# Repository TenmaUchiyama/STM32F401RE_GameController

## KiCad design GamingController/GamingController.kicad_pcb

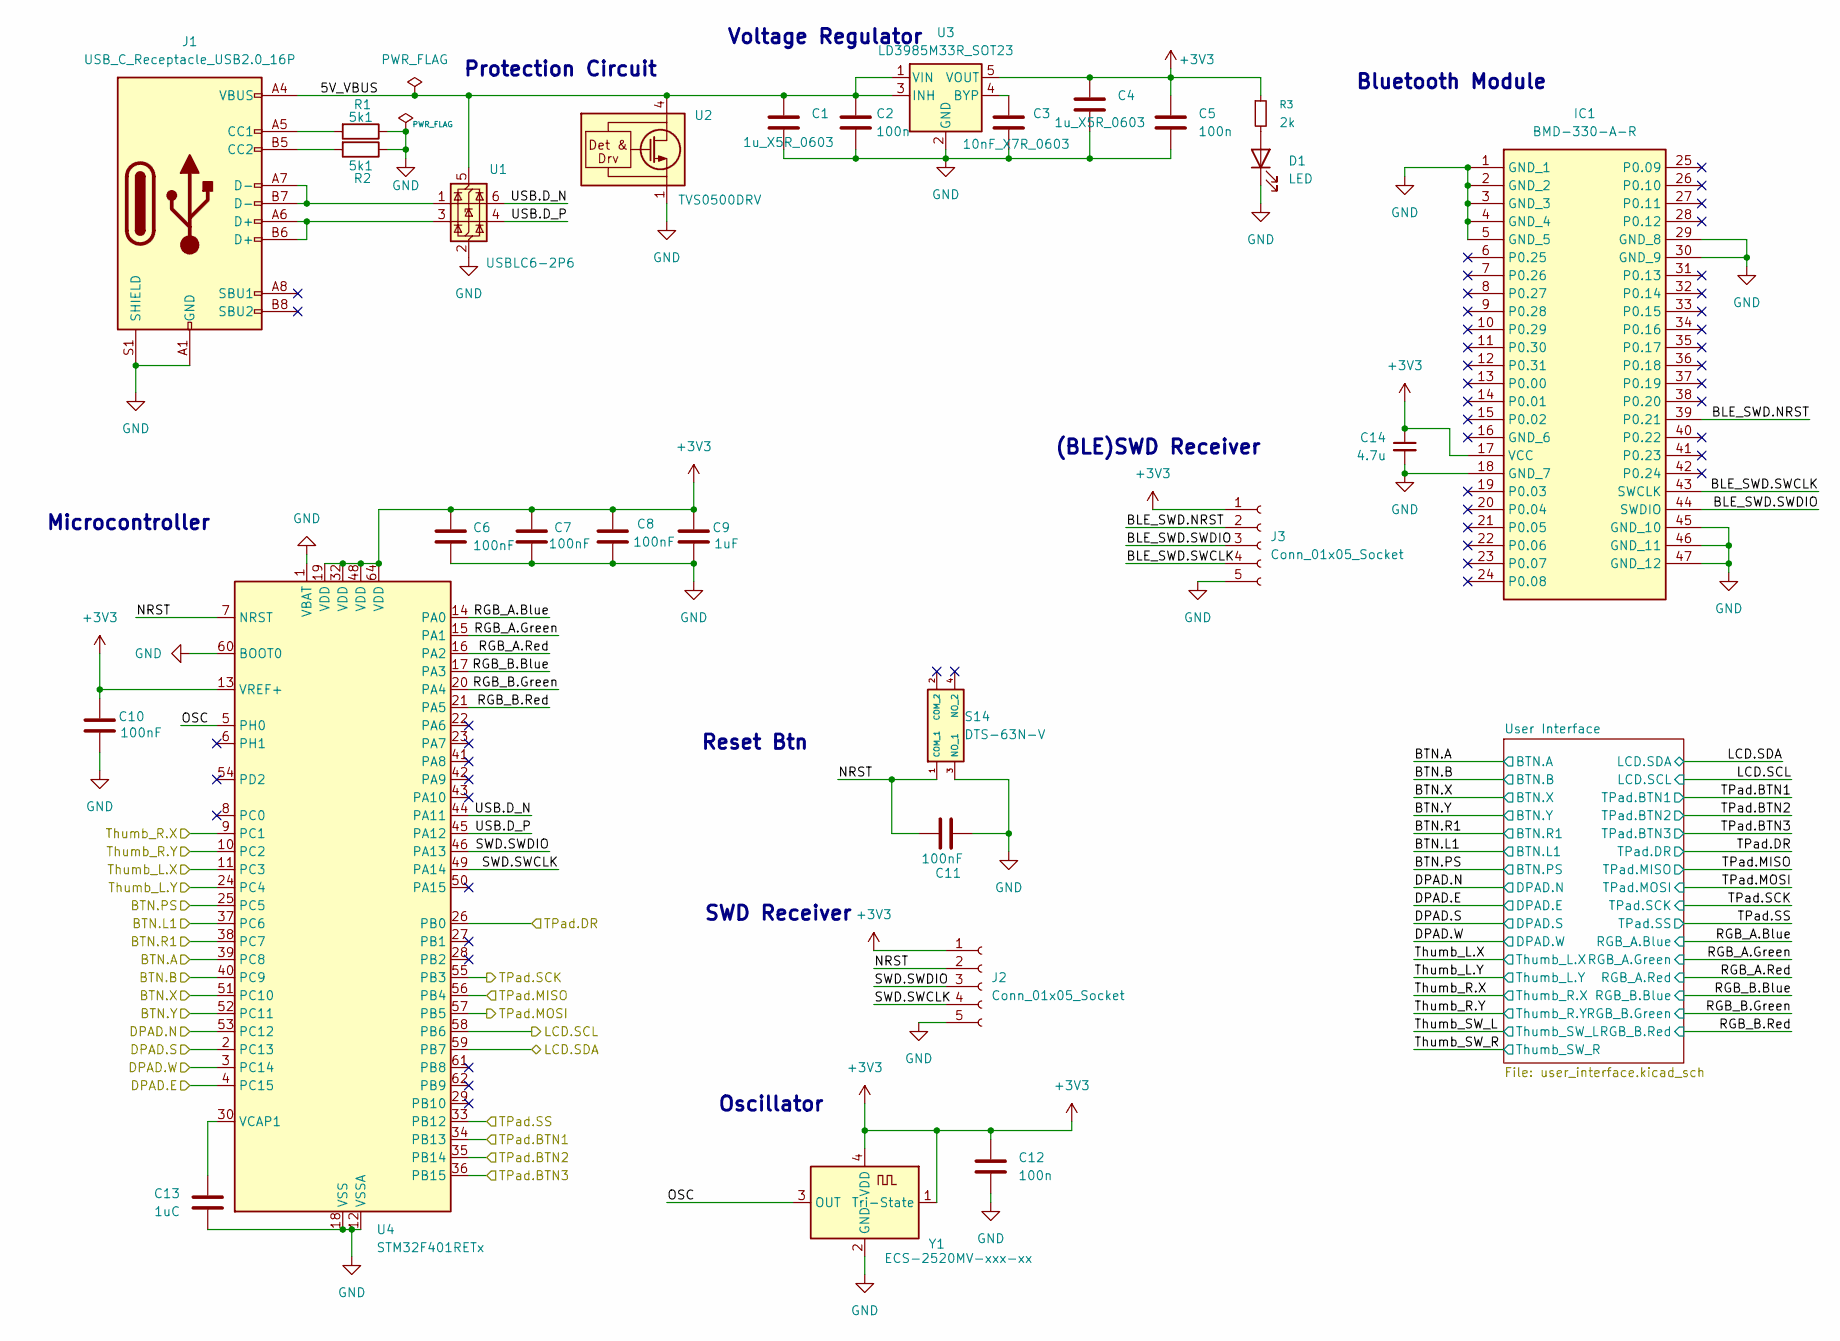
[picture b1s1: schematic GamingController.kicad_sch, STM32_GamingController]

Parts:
C1, C4: 1u_X5R_0603; C_0201_0603Metric
C2, C5, C12: 100n; C_0201_0603Metric
C3: 10nF_X7R_0603; C_0201_0603Metric
C6, C7, C8, C10, C11: 100nF; C_0201_0603Metric
C9: 1uF; C_0201_0603Metric
C13: 1uC; C_0201_0603Metric
C14: 4.7u; C_0201_0603Metric
D1: LED; LED_0201_0603Metric
IC1: BMD-330-A-R; BMD330AR; Mouser Part Number 377-BMD-330-A-R
J1: USB_C_Receptacle_USB2.0_16P; USB_C_Receptacle_JAE_DX07S016JA1R1500
J2, J3: Conn_01x05_Socket; PinSocket_1x05_P2.00mm_Horizontal
R1, R2: 5k1; R_0201_0603Metric
R3: 2k; R_0201_0603Metric
S14: DTS-63N-V; DTS63NV; Mouser Part Number 113-DTS-63N-V
U1: USBLC6-2P6; SOT-666
U2: TVS0500DRV; WSON-6-1EP_2x2mm_P0.65mm_EP1x1.6mm
U3: LD3985M33R_SOT23; SOT-23-5
U4: STM32F401RETx; LQFP-64_10x10mm_P0.5mm
Y1: ECS-2520MV-xxx-xx; Oscillator_SMD_ECS_2520MV-xxx-xx-4Pin_2.5x2.0mm

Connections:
+3V3: C4.1, C5.1, C6.1, C7.1, C8.1, C9.1, C10.1, C12.1, C14.1, IC1.17 (VCC), J2.1, J3.1, R3.1, U3.5 (VOUT), U4.13 (VREF+), U4.19 (VDD), U4.32 (VDD), U4.48 (VDD), U4.64 (VDD), Y1.1 (Tri-State), Y1.4 (VDD); also elsewhere on the board
/5V_VBUS: C1.1, C2.1, J1.A4 (VBUS), J1.A9 (VBUS), J1.B4 (VBUS), J1.B9 (VBUS), U1.5 (VBUS), U2.4 (IN), U2.5 (IN), U2.6 (IN), U3.1 (VIN), U3.3 (INH)
/BLE_SWD.NRST: IC1.39 (P0.21), J3.2
/BLE_SWD.SWCLK: IC1.43 (SWCLK), J3.4
/BLE_SWD.SWDIO: IC1.44 (SWDIO), J3.3
/BTN.A: U4.39 (PC8); also elsewhere on the board
/BTN.B: U4.40 (PC9); also elsewhere on the board
/BTN.L1: U4.37 (PC6); also elsewhere on the board
/BTN.PS: U4.25 (PC5); also elsewhere on the board
/BTN.R1: U4.38 (PC7); also elsewhere on the board
/BTN.X: U4.51 (PC10); also elsewhere on the board
/BTN.Y: U4.52 (PC11); also elsewhere on the board
/DPAD.E: U4.4 (PC15); also elsewhere on the board
/DPAD.N: U4.53 (PC12); also elsewhere on the board
/DPAD.S: U4.2 (PC13); also elsewhere on the board
/DPAD.W: U4.3 (PC14); also elsewhere on the board
/LCD.SCL: U4.58 (PB6); also elsewhere on the board
/LCD.SDA: U4.59 (PB7); also elsewhere on the board
/NRST: C11.1, J2.2, S14.1 (COM_1), U4.7 (NRST)
/OSC: U4.5 (PH0), Y1.3 (OUT)
/RGB_A.Blue: U4.14 (PA0); also elsewhere on the board
/RGB_A.Green: U4.15 (PA1); also elsewhere on the board
/RGB_A.Red: U4.16 (PA2); also elsewhere on the board
/RGB_B.Blue: U4.17 (PA3); also elsewhere on the board
/RGB_B.Green: U4.20 (PA4); also elsewhere on the board
/RGB_B.Red: U4.21 (PA5); also elsewhere on the board
/SWD.SWCLK: J2.4, U4.49 (PA14)
/SWD.SWDIO: J2.3, U4.46 (PA13)
/TPad.BTN1: U4.34 (PB13); also elsewhere on the board
/TPad.BTN2: U4.35 (PB14); also elsewhere on the board
/TPad.BTN3: U4.36 (PB15); also elsewhere on the board
/TPad.DR: U4.26 (PB0); also elsewhere on the board
/TPad.MISO: U4.56 (PB4); also elsewhere on the board
/TPad.MOSI: U4.57 (PB5); also elsewhere on the board
/TPad.SCK: U4.55 (PB3); also elsewhere on the board
/TPad.SS: U4.33 (PB12); also elsewhere on the board
/Thumb_L.X: U4.11 (PC3); also elsewhere on the board
/Thumb_L.Y: U4.24 (PC4); also elsewhere on the board
/Thumb_R.X: U4.9 (PC1); also elsewhere on the board
/Thumb_R.Y: U4.10 (PC2); also elsewhere on the board
/USB.D_N: U1.6 (I/O1), U4.44 (PA11)
/USB.D_P: U1.4 (I/O2), U4.45 (PA12)
GND: C1.2, C2.2, C3.2, C4.2, C5.2, C6.2, C7.2, C8.2, C9.2, C10.2, C11.2, C12.2, C13.2, C14.2, D1.1 (K), IC1.1 (GND_1), IC1.2 (GND_2), IC1.3 (GND_3), IC1.4 (GND_4), IC1.5 (GND_5), IC1.18 (GND_7), IC1.29 (GND_8), IC1.30 (GND_9), IC1.45 (GND_10), IC1.46 (GND_11), IC1.47 (GND_12), J1.A1 (GND), J1.A12 (GND), J1.B1 (GND), J1.B12 (GND), J1.S1 (SHIELD), J2.5, J3.5, R1.1, R2.1, S14.3 (NO_1), U1.2 (GND), U2.1 (GND), U2.2 (GND), U2.3 (GND), U2.7 (GND), U3.2 (GND), U4.1 (VBAT), U4.12 (VSSA), U4.18 (VSS), U4.31 (VSS), U4.47 (VSS), U4.60 (BOOT0), U4.63 (VSS), Y1.2 (GND); also elsewhere on the board
unnamed: D1.2 (A), R3.2
unnamed: J1.A5 (CC1), R1.2
unnamed: J1.B5 (CC2), R2.2
unnamed: J1.A6 (D+), J1.B6 (D+), U1.3 (I/O2)
unnamed: J1.A7 (D-), J1.B7 (D-), U1.1 (I/O1)
unnamed: C3.1, U3.4 (BYP)
unnamed: C13.1, U4.30 (VCAP1)

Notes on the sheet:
Microcontroller
Bluetooth Module
Voltage Regulator
SWD Receiver
(BLE)SWD Receiver
Reset Btn
Protection Circuit
Oscillator

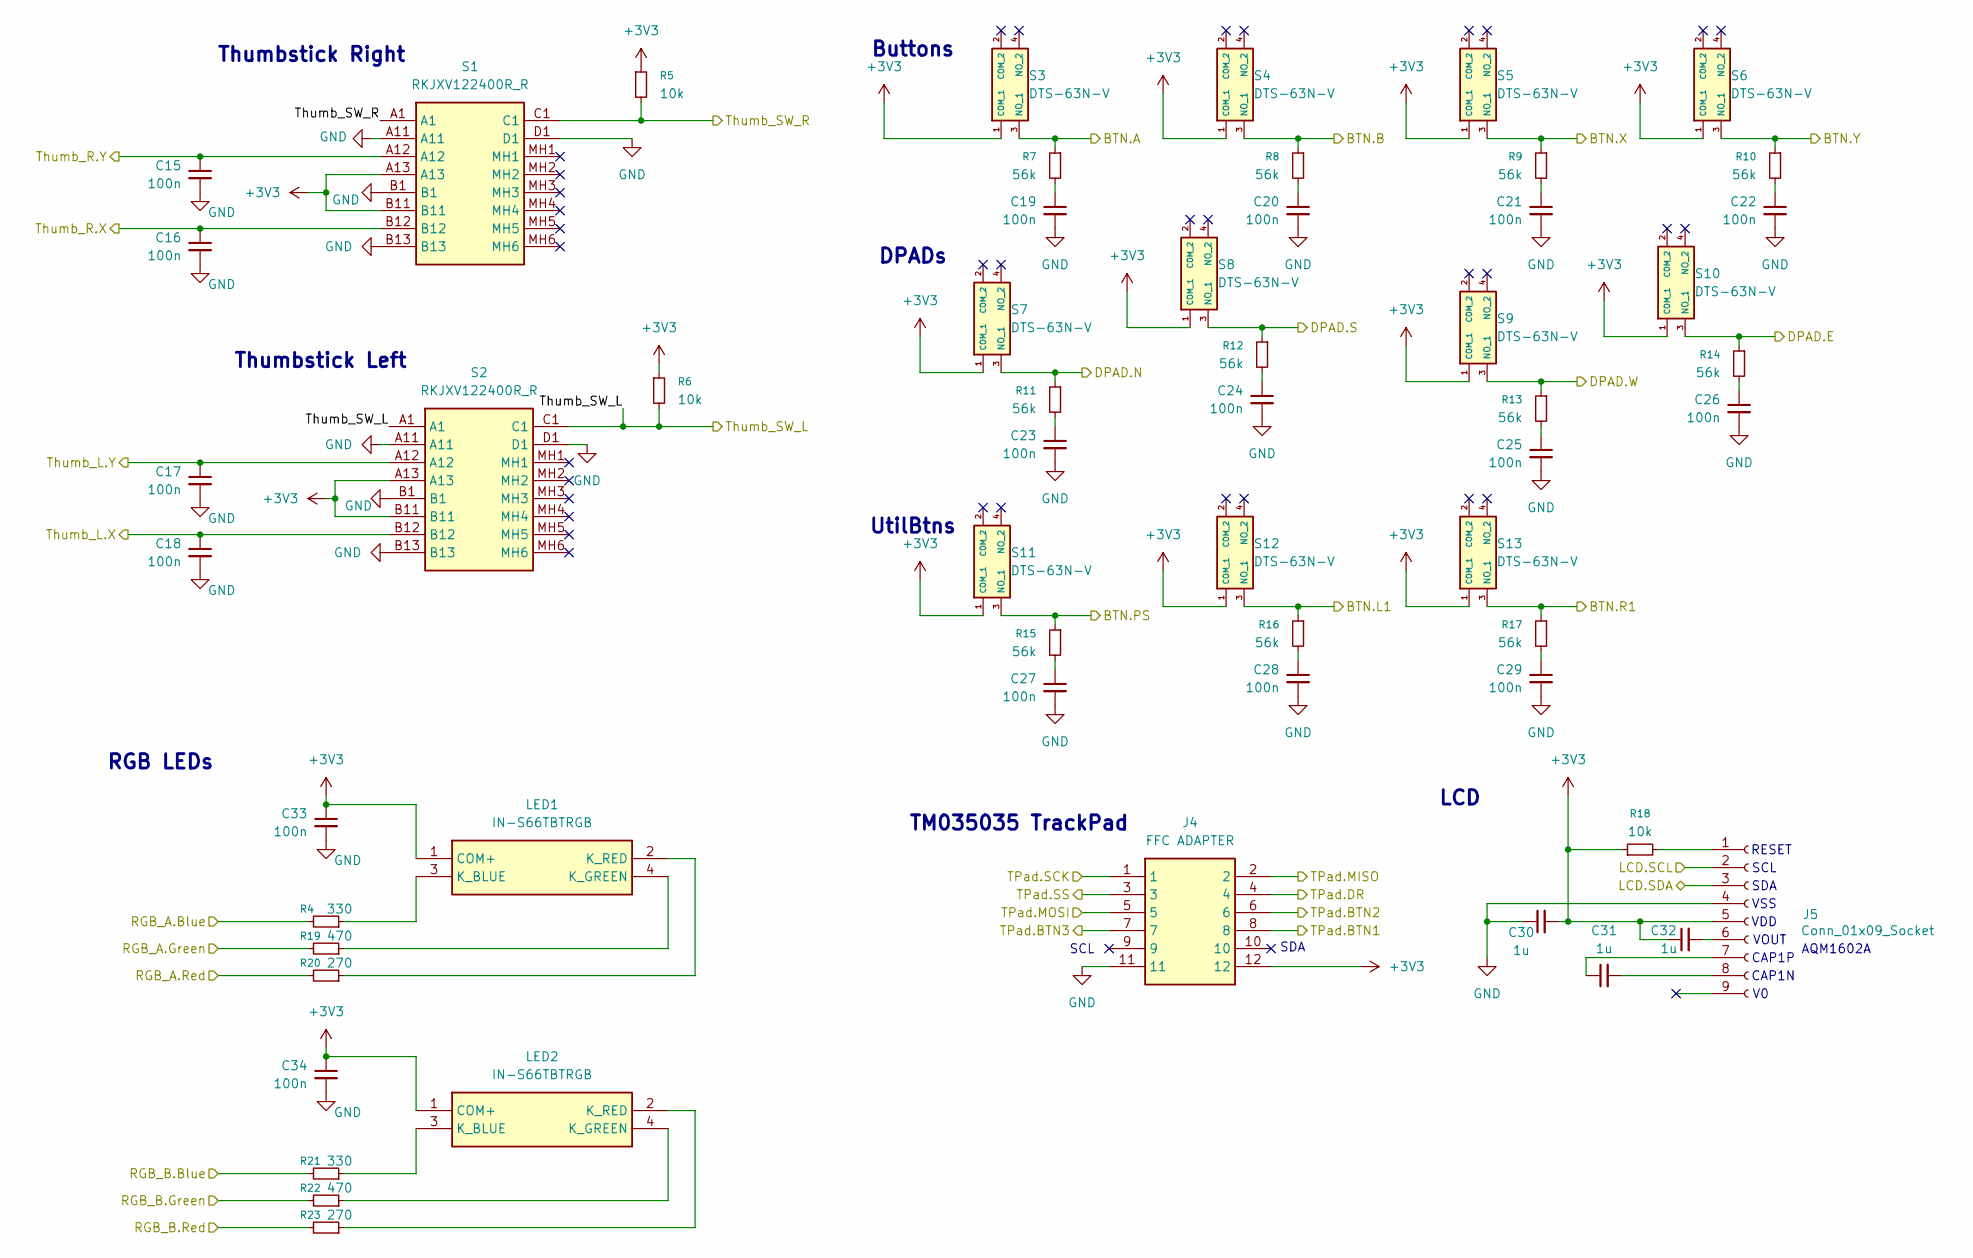
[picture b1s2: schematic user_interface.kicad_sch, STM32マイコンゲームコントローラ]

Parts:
C15, C16, C17, C18, C19, C20, C21, C22, C23, C24, C25, C26, C27, C28, C29, C33, C34: 100n; C_0201_0603Metric
C30, C31, C32: 1u; C_0201_0603Metric
J4: FFC ADAPTER; 0781271220; Mouser Part Number 538-78127-1220
J5: Conn_01x09_Socket; PinSocket_1x09_P1.27mm_Vertical
LED1, LED2: IN-S66TBTRGB; INS66TBTRGB; Mouser Part Number 743-IN-S66TBTRGB
R4, R21: 330; R_0201_0603Metric
R5, R6: 10k; R_0201_0603Metric
R7, R8, R9, R10, R11, R12, R13, R14, R15, R16: 56k; R_0201_0603Metric
R17: 56k; R_0201_0603Metric_Pad0.64x0.40mm_HandSolder
R18: 10k; R_0201_0603Metric_Pad0.64x0.40mm_HandSolder
R19, R22: 470; R_0201_0603Metric
R20, R23: 270; R_0201_0603Metric
S1, S2: RKJXV122400R_R; RKJXV122400R; Manufacturer_Part_Number RKJXV122400R; Mouser Part Number 688-RKJXV122400R
S3, S4, S5, S6, S7, S8, S9, S10, S11, S12, S13: DTS-63N-V; DTS63NV; Mouser Part Number 113-DTS-63N-V

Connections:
+3V3: C30.2, C32.1, C33.1, C34.1, J4.12, J5.5, LED1.1 (COM+), LED2.1 (COM+), R5.1, R6.1, R18.1, S1.A13, S1.B11, S2.A13, S2.B11, S3.1 (COM_1), S4.1 (COM_1), S5.1 (COM_1), S6.1 (COM_1), S7.1 (COM_1), S8.1 (COM_1), S9.1 (COM_1), S10.1 (COM_1), S11.1 (COM_1), S12.1 (COM_1), S13.1 (COM_1); also elsewhere on the board
/BTN.A: R7.1, S3.3 (NO_1); also elsewhere on the board
/BTN.B: R8.1, S4.3 (NO_1); also elsewhere on the board
/BTN.L1: R16.1, S12.3 (NO_1); also elsewhere on the board
/BTN.PS: R15.1, S11.3 (NO_1); also elsewhere on the board
/BTN.R1: R17.1, S13.3 (NO_1); also elsewhere on the board
/BTN.X: R9.1, S5.3 (NO_1); also elsewhere on the board
/BTN.Y: R10.1, S6.3 (NO_1); also elsewhere on the board
/DPAD.E: R14.1, S10.3 (NO_1); also elsewhere on the board
/DPAD.N: R11.1, S7.3 (NO_1); also elsewhere on the board
/DPAD.S: R12.1, S8.3 (NO_1); also elsewhere on the board
/DPAD.W: R13.1, S9.3 (NO_1); also elsewhere on the board
/LCD.SCL: J5.2; also elsewhere on the board
/LCD.SDA: J5.3; also elsewhere on the board
/RGB_A.Blue: R4.2; also elsewhere on the board
/RGB_A.Green: R19.2; also elsewhere on the board
/RGB_A.Red: R20.2; also elsewhere on the board
/RGB_B.Blue: R21.2; also elsewhere on the board
/RGB_B.Green: R22.2; also elsewhere on the board
/RGB_B.Red: R23.2; also elsewhere on the board
/Thumb_L.X: C18.1, S2.B12; also elsewhere on the board
/Thumb_L.Y: C17.1, S2.A12; also elsewhere on the board
/Thumb_R.X: C16.1, S1.B12; also elsewhere on the board
/Thumb_R.Y: C15.1, S1.A12; also elsewhere on the board
/Thumb_SW_L: R6.2, S2.A1, S2.C1
/Thumb_SW_R: R5.2, S1.A1, S1.C1
GND: C15.2, C16.2, C17.2, C18.2, C19.2, C20.2, C21.2, C22.2, C23.2, C24.2, C25.2, C26.2, C27.2, C28.2, C29.2, C30.1, C33.2, C34.2, J4.11, J5.4, S1.A11, S1.B1, S1.B13, S1.D1, S2.A11, S2.B1, S2.B13, S2.D1; also elsewhere on the board
unnamed: C19.1, R7.2
unnamed: C20.1, R8.2
unnamed: C21.1, R9.2
unnamed: C22.1, R10.2
unnamed: C23.1, R11.2
unnamed: C24.1, R12.2
unnamed: C25.1, R13.2
unnamed: C26.1, R14.2
unnamed: C27.1, R15.2
unnamed: C28.1, R16.2
unnamed: C29.1, R17.2
unnamed: J5.1, R18.2
unnamed: C32.2, J5.6
unnamed: C31.1, J5.7
unnamed: C31.2, J5.8
unnamed: LED1.3 (K_BLUE), R4.1
unnamed: LED1.4 (K_GREEN), R19.1
unnamed: LED1.2 (K_RED), R20.1
unnamed: LED2.3 (K_BLUE), R21.1
unnamed: LED2.4 (K_GREEN), R22.1
unnamed: LED2.2 (K_RED), R23.1

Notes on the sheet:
TM035035 TrackPad
LCD
DPADs
AQM1602A
Buttons
Thumbstick Right
UtilBtns
CAP1N
SCL
RESET
SDA
VOUT
SCL
VDD
CAP1P
RGB LEDs
Thumbstick Left
VSS

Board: 2 copper layers, 85 parts (0 on the bottom side), 73 nets, no tracks yet.

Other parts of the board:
J4_TPAD: FFC ADAPTER; 0781271220

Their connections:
+3V3: J4_TPAD.12; also elsewhere on the board
/TPad.BTN1: J4_TPAD.8; also elsewhere on the board
/TPad.BTN2: J4_TPAD.6; also elsewhere on the board
/TPad.BTN3: J4_TPAD.7; also elsewhere on the board
/TPad.DR: J4_TPAD.4; also elsewhere on the board
/TPad.MISO: J4_TPAD.2; also elsewhere on the board
/TPad.MOSI: J4_TPAD.5; also elsewhere on the board
/TPad.SCK: J4_TPAD.1; also elsewhere on the board
/TPad.SS: J4_TPAD.3; also elsewhere on the board
GND: J4_TPAD.11; also elsewhere on the board

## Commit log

2025-08-02 Added Some
2025-08-05 forgot to save
2025-08-06 Draw Schematics
2025-08-07 Schematics Done
